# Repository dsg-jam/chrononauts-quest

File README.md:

# Chrononauts Quest

## Board

## Website

## Backend

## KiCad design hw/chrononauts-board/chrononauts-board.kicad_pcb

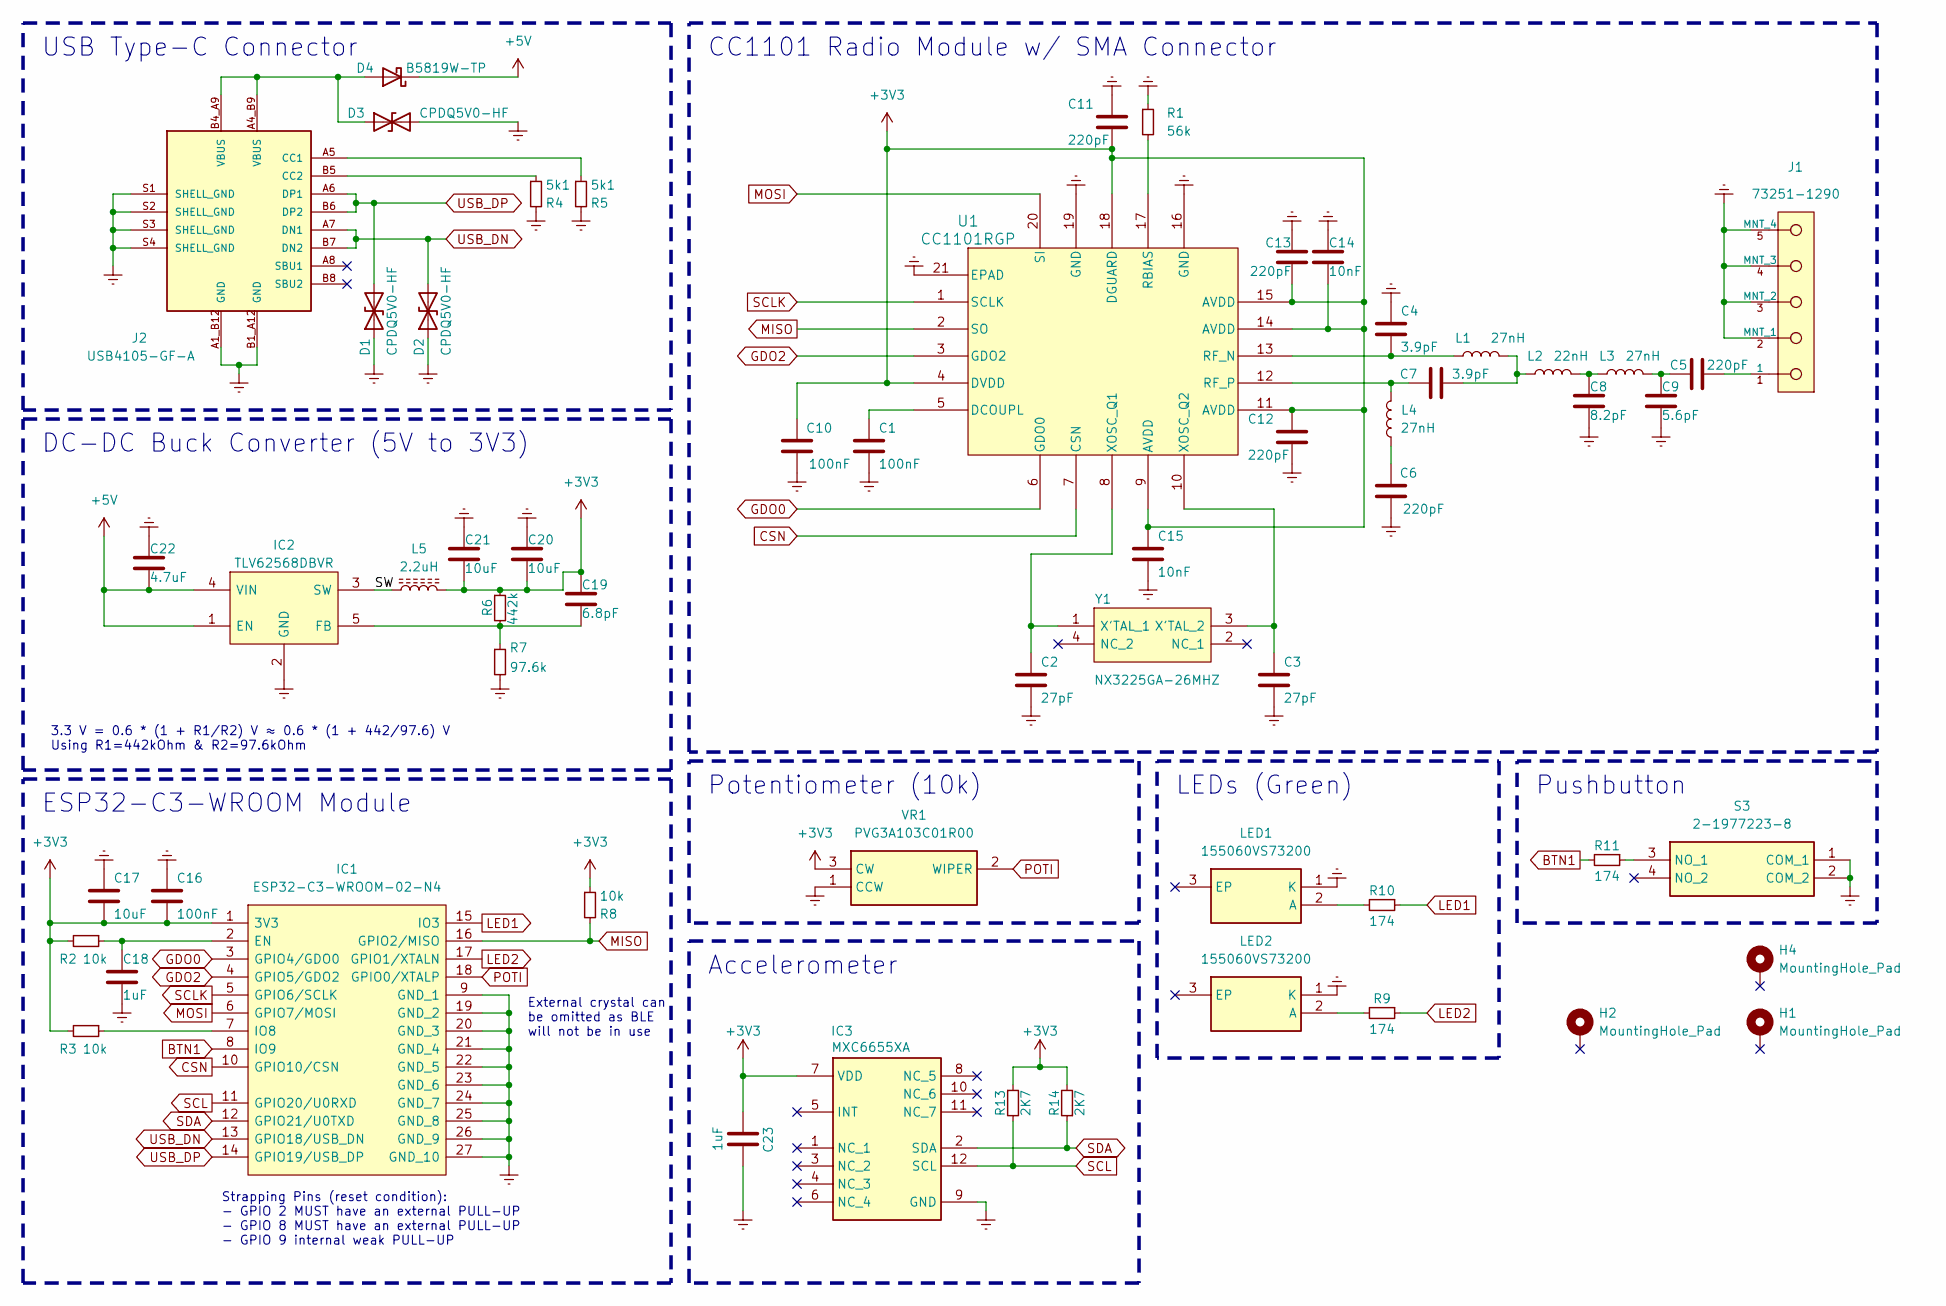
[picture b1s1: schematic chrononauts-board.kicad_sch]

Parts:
C1, C10, C16: 100nF; Cap_Murata_GRM_0402; LCSC C431646
C2, C3: 27pF; Cap_Murata_GRM_0402; LCSC C342944
C4, C7: 3.9pF; Cap_Murata_GRM_0402; LCSC C565491
C5, C6, C11, C12, C13: 220pF; Cap_Murata_GRM_0402; LCSC C412611
C8: 8.2pF; Cap_Murata_GRM_0402; LCSC C393674
C9: 5.6pF; Cap_Murata_GRM_0402; LCSC C525219
C14, C15: 10nF; Cap_Murata_GRM_0402; LCSC C482489
C17, C20, C21: 10uF; Cap_Murata_GRM_0402; LCSC C510630
C18, C23: 1uF; Cap_Murata_GRM_0402; LCSC C527012
C19: 6.8pF; Cap_Murata_GRM_0402; LCSC C338054
C22: 4.7uF; Cap_Murata_GRM_0603; LCSC C77045
D1, D2, D3: CPDQ5V0-HF; SODFL1006X40N; LCSC C2441615
D4: B5819W-TP; SOD3716X135N; LCSC C84354
H1, H2, H4: MountingHole_Pad; MountingHole_2.2mm_M2_DIN965_Pad_TopBottom
IC1: ESP32-C3-WROOM-02-N4; ESP32C3WROOM02N4; Mouser Part Number 356-ESP32C3WROOM02N4
IC2: TLV62568DBVR; Mouser Part Number 595-TLV62568DBVR
IC3: MXC6655XA; Mouser Part Number 438-MXC6655XA
J1: 73251-1290; Molex-SD-73251-129; mouser part number 538-73251-1290; digikey description SMA Connector Jack, Female Socket 50 Oh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
J2: USB4105-GF-A; GCT_USB4105-GF-A; PARTREV A3; LCSC C3020560
L1, L3, L4: 27nH; L_Murata_LQG_0402; LCSC C12669
L2: 22nH; L_Murata_LQG_0402; LCSC C12670
L5: 2.2uH; ASPI0418FS; LCSC C2042636
LED1, LED2: 155060VS73200; Mouser Part Number 710-155060VS73200
R1: 56k; R_KOA_RK_0402; LCSC C71703
R2, R3, R8: 10k; R_Vishay_CRCW_0402; LCSC C471764
R4, R5: 5k1; R_Vishay_CRCW_0402; LCSC C138073
R6: 442k; R_Bourns_CR_0603; LCSC C234533
R7: 97.6k; R_Bourns_CR_0603; LCSC C507495
R9, R10, R11: 174; R_Vishay_CRCW_0402; LCSC C416364
R13, R14: 2K7; R_Vishay_CRCW_0402; LCSC C416505
S3: 2-1977223-8; 219772238; Mouser Part Number 506-2-1977223-8
U1: CC1101RGP
VR1: PVG3A103C01R00; Mouser Part Number 81-PVG3A103C01R00
Y1: NX3225GA-26MHZ; NX3225GA16000MSTDCRG1; Mouser Part Number 344-NX3225GA26MHZEXS

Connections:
+3V3: C10.2, C11.2, C12.1, C13.2, C14.2, C15.1, C16.2, C17.2, C19.2, C20.2, C21.2, C23.1, IC1.1 (3V3), IC3.7 (VDD), L5.2, R2.2, R3.2, R6.1, R8.1, R13.1, R14.2, U1.4 (DVDD), U1.9 (AVDD), U1.11 (AVDD), U1.14 (AVDD), U1.15 (AVDD), U1.18 (DGUARD), VR1.3 (CW)
+5V: C22.1, D4.1 (K), IC2.1 (EN), IC2.4 (VIN)
/SW: IC2.3 (SW), L5.1
BTN1: IC1.8 (IO9), R11.2
CSN: IC1.10 (GPIO10/CSN), U1.7 (CSN)
Earth: C1.2, C2.2, C3.2, C4.1, C6.1, C8.1, C9.1, C10.1, C11.1, C12.2, C13.1, C14.1, C15.2, C16.1, C17.1, C18.2, C20.1, C21.1, C22.2, C23.2, D1.1 (A1), D2.1 (A1), D3.2 (A2), IC1.9 (GND_1), IC1.19 (GND_2), IC1.20 (GND_3), IC1.21 (GND_4), IC1.22 (GND_5), IC1.23 (GND_6), IC1.24 (GND_7), IC1.25 (GND_8), IC1.26 (GND_9), IC1.27 (GND_10), IC2.2 (GND), IC3.9 (GND), J1.2 (MNT_1), J1.3 (MNT_2), J1.4 (MNT_3), J1.5 (MNT_4), J2.A1_B12 (GND), J2.B1_A12 (GND), J2.S1 (SHELL_GND), J2.S2 (SHELL_GND), J2.S3 (SHELL_GND), J2.S4 (SHELL_GND), LED1.1 (K), LED2.1 (K), R1.1, R4.2, R5.2, R7.2, S3.1 (COM_1), S3.2 (COM_2), U1.16 (GND), U1.19 (GND), U1.21 (EPAD), VR1.1 (CCW)
GDO0: IC1.3 (GPIO4/GDO0), U1.6 (GDO0)
GDO2: IC1.4 (GPIO5/GDO2), U1.3 (GDO2)
LED1: IC1.15 (IO3), R10.1
LED2: IC1.17 (GPIO1/XTALN), R9.1
MISO: IC1.16 (GPIO2/MISO), R8.2, U1.2 (SO)
MOSI: IC1.6 (GPIO7/MOSI), U1.20 (SI)
unnamed: C5.1, C9.2, L3.2
unnamed: C5.2, J1.1
unnamed: C6.2, L4.1
unnamed: C7.2, L1.2, L2.1
unnamed: C8.2, L2.2, L3.1
unnamed: D3.1 (A1), D4.2 (A), J2.A4_B9 (VBUS), J2.B4_A9 (VBUS)
unnamed: C18.1, IC1.2 (EN), R2.1
unnamed: IC1.7 (IO8), R3.1
unnamed: C19.1, IC2.5 (FB), R6.2, R7.1
unnamed: J2.A5 (CC1), R5.1
unnamed: J2.B5 (CC2), R4.1
unnamed: LED1.2 (A), R10.2
unnamed: LED2.2 (A), R9.2
unnamed: R11.1, S3.3 (NO_1)
unnamed: C1.1, U1.5 (DCOUPL)
unnamed: R1.2, U1.17 (RBIAS)
unnamed: C4.2, L1.1, U1.13 (RF_N)
unnamed: C7.1, L4.2, U1.12 (RF_P)
unnamed: C2.1, U1.8 (XOSC_Q1), Y1.1 (X'TAL_1)
unnamed: C3.1, U1.10 (XOSC_Q2), Y1.3 (X'TAL_2)
POTI: IC1.18 (GPIO0/XTALP), VR1.2 (WIPER)
SCL: IC1.11 (GPIO20/U0RXD), IC3.12 (SCL), R13.2
SCLK: IC1.5 (GPIO6/SCLK), U1.1 (SCLK)
SDA: IC1.12 (GPIO21/U0TXD), IC3.2 (SDA), R14.1
USB_DN: D2.2 (A2), IC1.13 (GPIO18/USB_DN), J2.A7 (DN1), J2.B7 (DN2)
USB_DP: D1.2 (A2), IC1.14 (GPIO19/USB_DP), J2.A6 (DP1), J2.B6 (DP2)

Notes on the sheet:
Strapping Pins (reset condition): - GPIO 2 MUST have an external PULL-UP - GPIO 8 MUST have an external PULL-UP - GPIO 9 internal weak PULL-UP
Pushbutton
CC1101 Radio Module w/ SMA Connector
3.3 V = 0.6 * (1 + R1/R2) V ≈ 0.6 * (1 + 442/97.6) V Using R1=442kOhm & R2=97.6kOhm
DC-DC Buck Converter (5V to 3V3)
Accelerometer
LEDs (Green)
ESP32-C3-WROOM Module
External crystal can be omitted as BLE will not be in use
Potentiometer (10k)
USB Type-C Connector

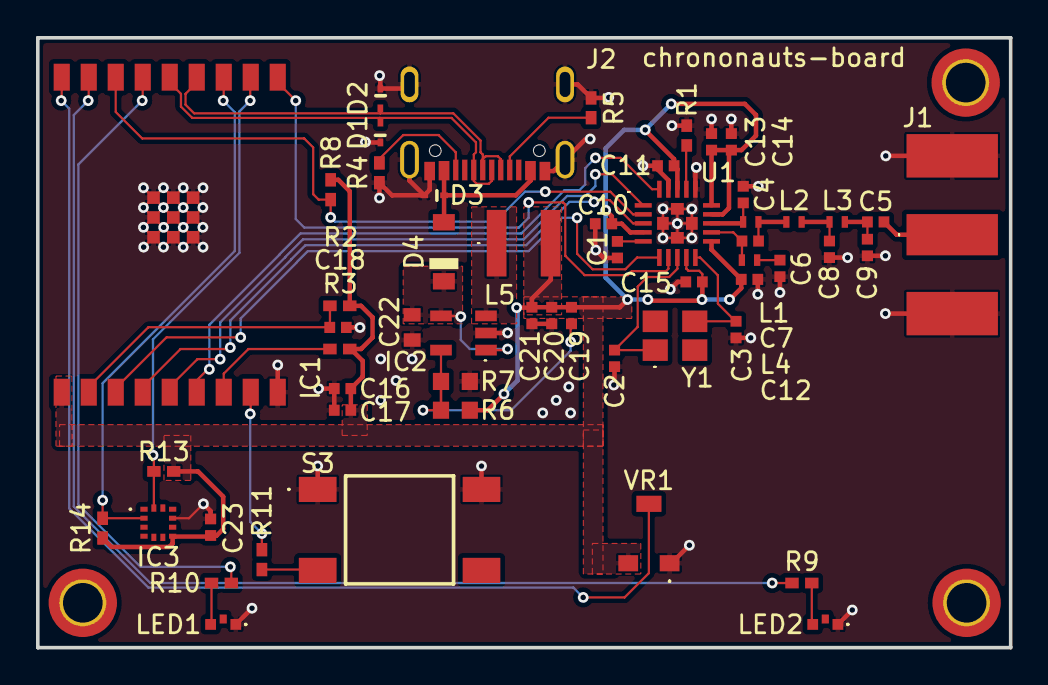
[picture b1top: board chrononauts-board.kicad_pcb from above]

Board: 2 copper layers, 54.0 x 33.9 mm, 59 parts (0 on the bottom side), 38 nets.

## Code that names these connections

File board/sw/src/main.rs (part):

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
    let spi_driver = SpiDriver::new(
        peripherals.spi2,
        pins.gpio6,
        pins.gpio7,
        Some(pins.gpio2),
        &DriverConfig::default().dma(Dma::Auto(4096)),
    )?;

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        scl_pullup_enabled: false,
        ..Default::default()
    };
    let i2c_driver = I2cDriver::new(peripherals.i2c0, pins.gpio21, pins.gpio20, &i2c_config)?;

    let spi_device_driver =
        SpiDeviceDriver::new(spi_driver, Some(pins.gpio10), &Config::default())?;

    let cc1101 = Cc1101::new(spi_device_driver).unwrap();

    let mut push_button = PinDriver::input(pins.gpio9)?;
    push_button.set_pull(Pull::Up)?;

    let led1 = PinDriver::output(pins.gpio3)?;
    let led2 = PinDriver::output(pins.gpio1)?;

    let poti_adc = AdcDriver::new(peripherals.adc1)?;

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    // #########################
    let mut potentiometer = ChrononautsPotentiometer::new(poti_adc, chrononauts_event_loop.clone())
        .expect("Potentiometer init failed");
    let _turning_knob_handler = { thread::spawn(move || potentiometer.run(pins.gpio0)) };

    // ################
    // # LEDs handler #
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
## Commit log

2024-05-31 add concept
2024-06-01 add preliminary landing page
2024-06-01 add questions and story brief
2024-06-01 Update MIT license
2024-06-01 add initial stuff
2024-06-01 normalize file endings
2024-06-01 add first blog post
2024-06-01 add question about ink spot
2024-06-01 add final psd project file
2024-06-01 add github actions for blog
2024-06-01 build manually
2024-06-01 rebuild if workflow changes
2024-06-01 bump ruby version
2024-06-01 allow image links to work
2024-06-29 init hw design
2024-06-29 hw: add libraries
2024-06-29 preliminary design
2024-06-29 hw: add README.md
2024-06-29 hw: update library
2024-06-30 hw: generate fab outputs
2024-06-30 hw: add assembly files
2024-07-01 hw: add preliminary firmware with captive portal
2024-07-22 add LEDs, push button, potentiometer and I2C accelerometer (preliminary)
2024-07-22 update PCB library
2024-07-27 ready for production
2024-08-05 Update BOM
2024-08-05 generate production files
2024-08-06 HW: Update assembly and production data
2024-08-06 HW: Update components library
2024-08-11 move devcontainer to blog dir
2024-08-11 create devcontainer for board sw
2024-08-11 add linked project
2024-08-11 devcontainer: add more dependencies
2024-08-11 devcontainer: add rustfmt
2024-08-11 devcontainer: add clippy
2024-08-11 bump dependencies and fix resulting errors
2024-08-11 Working test example to send messages via cc1101
2024-08-11 adapt ESP IDF version
2024-08-12 Replace direct register manipulation with wrapper calls
2024-08-12 change error handling in radio module
2024-08-12 set deviation according to datasheet
2024-08-13 adjust max dvga setting and comment some settings
2024-08-13 adapt power level type from cc1101 crate
2024-08-13 adds basic communication protocol
2024-08-15 Implements a simple game-loop
2024-08-15 devcontainer: install gcloud and node
2024-08-15 initialize website
2024-08-15 devcontainer: parallelize build and add gcloud to path
2024-08-17 fix devcontainer parallel install
2024-08-17 add backend crate and unify gitignore
2024-08-18 add website terminal renderer draft
2024-08-18 add backend api crate
2024-08-18 devcontainer: fix gcloud install
2024-08-18 accept initial connection
2024-08-18 read stuff from env
2024-08-19 adopt google cloud logging format
2024-08-19 read the correct client ip from headers
2024-08-19 only use gcloud logging for release builds
2024-08-19 add target label to gcloud logging
2024-08-19 start labyrinth state
2024-08-19 log x-forwarded-for parsing
2024-08-19 move board ws handler to separate module
2024-08-19 clippy
2024-08-19 log ignored messages
2024-08-20 start working on the website connection
2024-08-21 implement flow up to the labyrinth
2024-08-22 accept the first x-forwarded-for ip
2024-08-22 implement labyrinth movement
2024-08-23 add back missing gitignore line
2024-08-24 add gitlens to devcontainer
2024-08-24 first fully react based approach that isn't really going anywhere
2024-08-24 start of procedural approach
2024-08-26 preliminary game-loop
2024-08-26 move hardware into board dir
2024-08-26 move board-software into board dir
2024-08-26 fix devcontainer
2024-08-26 replace event id binary strings with CStr
2024-08-28 add 3-axis accelerometer handler and ws transmission handler
2024-08-28 move accelerometer handling code into peripherals module and restructured WebSocket Client
2024-08-28 Marking/Commenting main components
2024-08-28 move LEDs and potentiometer logic into dedicated modules
2024-08-28 handle button press in level 4
2024-08-28 Move game loop logic into dedicated module
2024-08-29 game-loop working, but not yet finished
2024-08-29 allow secondary board to reboot during game-loop and adjust packet window
2024-08-29 we can boot
2024-08-29 tidying up led handler
2024-08-29 improve the login flow
2024-08-29 use stored login creds if available
2024-08-29 add connection timeout
2024-08-29 increase terminal height
2024-08-29 make things work on smaller screens
2024-08-29 add simple labyrinth parser and move logic
2024-08-29 add command handling
2024-08-29 add labyrinth winning condition
2024-08-29 add conninfo and decrypt commands
2024-08-29 fix terminal x overflow
2024-08-29 set the websocket endpoint for prod
2024-08-29 enables api to handle board connection status
2024-08-30 Tested and adjusted game-loop
2024-08-30 uptade board-sw README.md
2024-08-30 Track and communicate connection status of the second board
2024-08-30 change heartbeat interval
2024-08-30 use env var to control skipping the boot animation
2024-08-30 store labyrinth state
2024-08-30 make the conninfo more consistent
2024-08-30 allow the websocket to reconnect
2024-08-30 fix terminal history and suppress spell checking
2024-08-30 skip boot animation should also skip cred cache stuff
2024-08-30 lazily copy lab layout
2024-08-30 fix newline behavior
2024-08-30 implement locate command
2024-08-30 Add lore
2024-08-30 make sure to scroll to the bottom of the terminal
2024-08-30 make cat print lines slightly faster
2024-08-30 hide walls in labyrinth until discovered
2024-08-30 formatting
2026-04-28 Add workflow_dispatch trigger to blog.yaml
